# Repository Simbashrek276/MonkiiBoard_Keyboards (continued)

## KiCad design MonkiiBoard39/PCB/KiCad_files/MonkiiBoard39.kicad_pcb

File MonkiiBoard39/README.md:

# MonkiiBoard39

The full keyboard of the family. Thirty nine keys packed into a tidy ortholinear 40 percent layout, running on a Pro Micro style ATmega32U4 board. It shows up to your computer as an ordinary USB keyboard, so there are no drivers to chase and nothing to set up on the host side.

## How it is wired

The switches sit in a grid of four rows and ten columns. The rows go to pins A3, A2, A1 and A0, and the columns go to pins 9, 8, 7, 6, 5, 4, 10, 16, 14 and 15. The firmware pulls one row low at a time and reads the columns through their internal pull up resistors, so a pressed key drags its column low and the scanner knows exactly which switch moved. There is a thirty millisecond debounce on every key so a single press only ever registers once.

This board runs without diodes. That keeps the build cheap and simple, and it is perfectly happy for everyday typing where you are hitting one or two keys at a time. Press a bunch of keys at once that happen to line up in the grid and you can get the usual ghosting any diodeless board has, so it is not the board for mashing five keys together.

## Two ways to build it

You can hand wire the whole thing to the pins listed above, same as I did with the very first one, or you can order the PCB I designed for it and solder onto that instead. Both run the same firmware and land on the exact same pins, no diodes either way.

The full story of how that board came together, along with the files to get one made, lives in the [PCB folder](PCB/).

## The layout

The three upper rows carry a familiar qwerty arrangement. The top row runs q across to p, the home row runs a across to l and finishes with backspace, and the lower letter row runs z through the comma and the period and finishes with enter.

The bottom row is where the fun is, and the firmware handles it by hand instead of pulling from the keymap table.

## Sticky modifiers

Control, shift and alt live on the first three keys of the bottom row, and they work as sticky modifiers. Tap one and it arms itself quietly, then the next key you press comes through with that modifier held, and the moment you let that key go the modifier clears itself again. So you can fire something like control and c without ever holding two keys down at the same time, which sits nicely with the diodeless matrix.

## The double tap Windows key

The fourth key on the bottom row is the Windows key, and it carries a little extra smarts. A single tap arms it as a sticky modifier just like the others, so you can build combos such as Windows and d. Tap it twice quickly, inside about a third of a second, and it fires the Windows key on its own to pop the start menu open.

## The spacebar

The space stretches across the middle of the bottom row as a wide 2u key. It is wired to two columns, five and six, so it registers a space no matter which side of the bar you happen to press.

## The case

The case folder holds the print ready plates for this board, a top plate that the switches clip into and a bottom plate that closes everything up. Drop them into your slicer as they are, no modelling needed. They come out nicely in PLA or PETG at around 0.2 millimeter layers with a few walls for a bit of stiffness.

## Flashing it

Open the sketch in the Arduino IDE, pick the Arduino Leonardo or SparkFun Pro Micro board and hit upload. It only needs the Keyboard library that already ships with the IDE, so there is nothing extra to install.

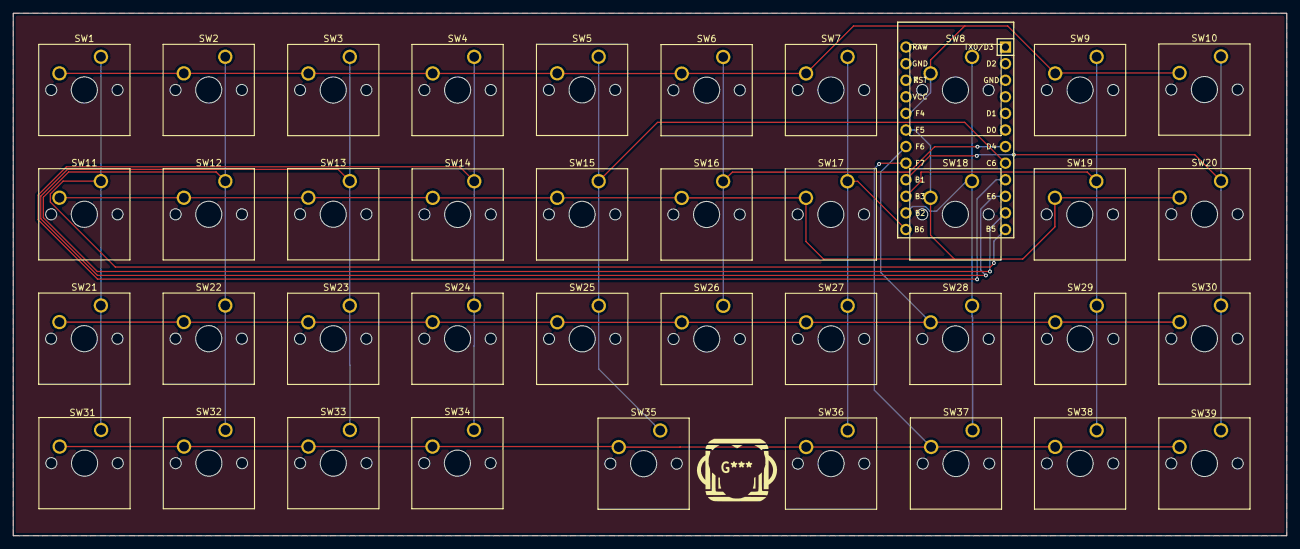
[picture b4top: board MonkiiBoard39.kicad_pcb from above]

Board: 2 copper layers, 195.0 x 80.0 mm, 40 parts (1 on the bottom side), 14 nets.

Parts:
SW1, SW2, SW3, SW4, SW5, SW6, SW7, SW8, SW9, SW10, SW11, SW12, SW13, SW14, SW15, SW16, SW17, SW18, SW19, SW20, SW21, SW22, SW23, SW24, SW25, SW26, SW27, SW28, SW29, SW30, SW31, SW32, SW33, SW34, SW35, SW36, SW37, SW38, SW39: Switch; SW_Cherry_MX_1.00u_PCB
U1: Arduino_Pro_Micro

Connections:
/Col1: SW1.1, SW11.1, SW21.1, SW31.1, U1.12 (9/PB5)
/Col2: SW2.1, SW12.1, SW22.1, SW32.1, U1.11 (8/PB4)
/Col3: SW3.1, SW13.1, SW23.1, SW33.1, U1.10 (7/PE6)
/Col4: SW4.1, SW14.1, SW24.1, SW34.1, U1.9 (6/PD7)
/Col5: SW5.1, SW15.1, SW25.1, SW35.1, U1.8 (5/PC6)
/Col6: SW6.1, SW16.1, SW26.1, U1.7 (4/PD4)
/Col7: SW7.1, SW17.1, SW27.1, SW36.1, U1.13 (10/PB6)
/Col8: SW8.1, SW18.1, SW28.1, SW37.1, U1.14 (16/PB2)
/Col9: SW9.1, SW19.1, SW29.1, SW38.1, U1.15 (14/PB3)
/Col10: SW10.1, SW20.1, SW30.1, SW39.1, U1.16 (15/PB1)
/Row1: SW1.2, SW2.2, SW3.2, SW4.2, SW5.2, SW6.2, SW7.2, SW8.2, SW9.2, SW10.2, U1.20 (A3/PF4)
/Row2: SW11.2, SW12.2, SW13.2, SW14.2, SW15.2, SW16.2, SW17.2, SW18.2, SW19.2, SW20.2, U1.19 (A2/PF5)
/Row3: SW21.2, SW22.2, SW23.2, SW24.2, SW25.2, SW26.2, SW27.2, SW28.2, SW29.2, SW30.2, U1.18 (A1/PF6)
/Row4: SW31.2, SW32.2, SW33.2, SW34.2, SW35.2, SW36.2, SW37.2, SW38.2, SW39.2, U1.17 (A0/PF7)

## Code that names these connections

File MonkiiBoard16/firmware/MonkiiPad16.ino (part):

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const int colPins[COL_NUM] = {0, 1, 2, 3};

// rotary encoder, A and B for turning plus the push switch
#define ENC_A   10
#define ENC_B   11
#define ENC_SW   8

// made up codes for the shortcut keys that arent normal ascii
#define K_EMPTY   0x00
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    pinMode(colPins[c], INPUT_PULLUP);
  }

  pinMode(ENC_A,  INPUT_PULLUP);
  pinMode(ENC_B,  INPUT_PULLUP);
  pinMode(ENC_SW, INPUT_PULLUP);
  encLastA = digitalRead(ENC_A);

  memset(keyState,       false, sizeof(keyState));
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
